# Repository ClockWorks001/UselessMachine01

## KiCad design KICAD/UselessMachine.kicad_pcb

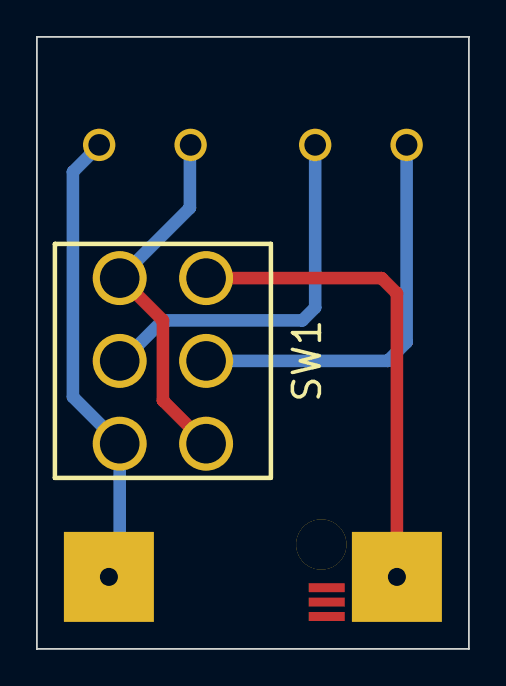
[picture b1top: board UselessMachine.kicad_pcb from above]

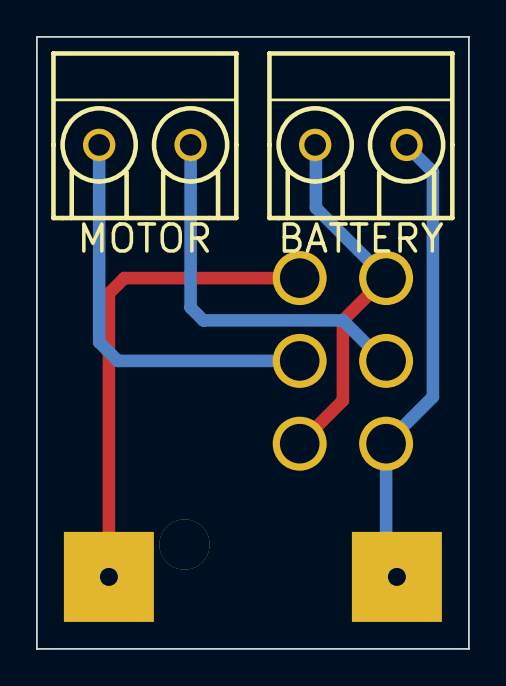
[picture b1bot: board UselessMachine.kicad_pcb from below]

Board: 2 copper layers, 24.0 x 34.0 mm, 5 parts (2 on the bottom side), 5 nets.

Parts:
BATTERY: CN_2P; TERMINAL_2P
MOTOR: CN_2P; TERMINAL_2P
P3_SW1, P4_SW1: CN_1P; PAD_1.0X5mm
SW1: SW_TOGGLE_6P_PANEL

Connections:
unnamed: BATTERY.2, P4_SW1.1, SW1.1
unnamed: BATTERY.1, SW1.3, SW1.4
unnamed: P3_SW1.1, SW1.6
unnamed: MOTOR.2, SW1.2
unnamed: MOTOR.1, SW1.5

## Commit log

2015-11-11 add ignore case
